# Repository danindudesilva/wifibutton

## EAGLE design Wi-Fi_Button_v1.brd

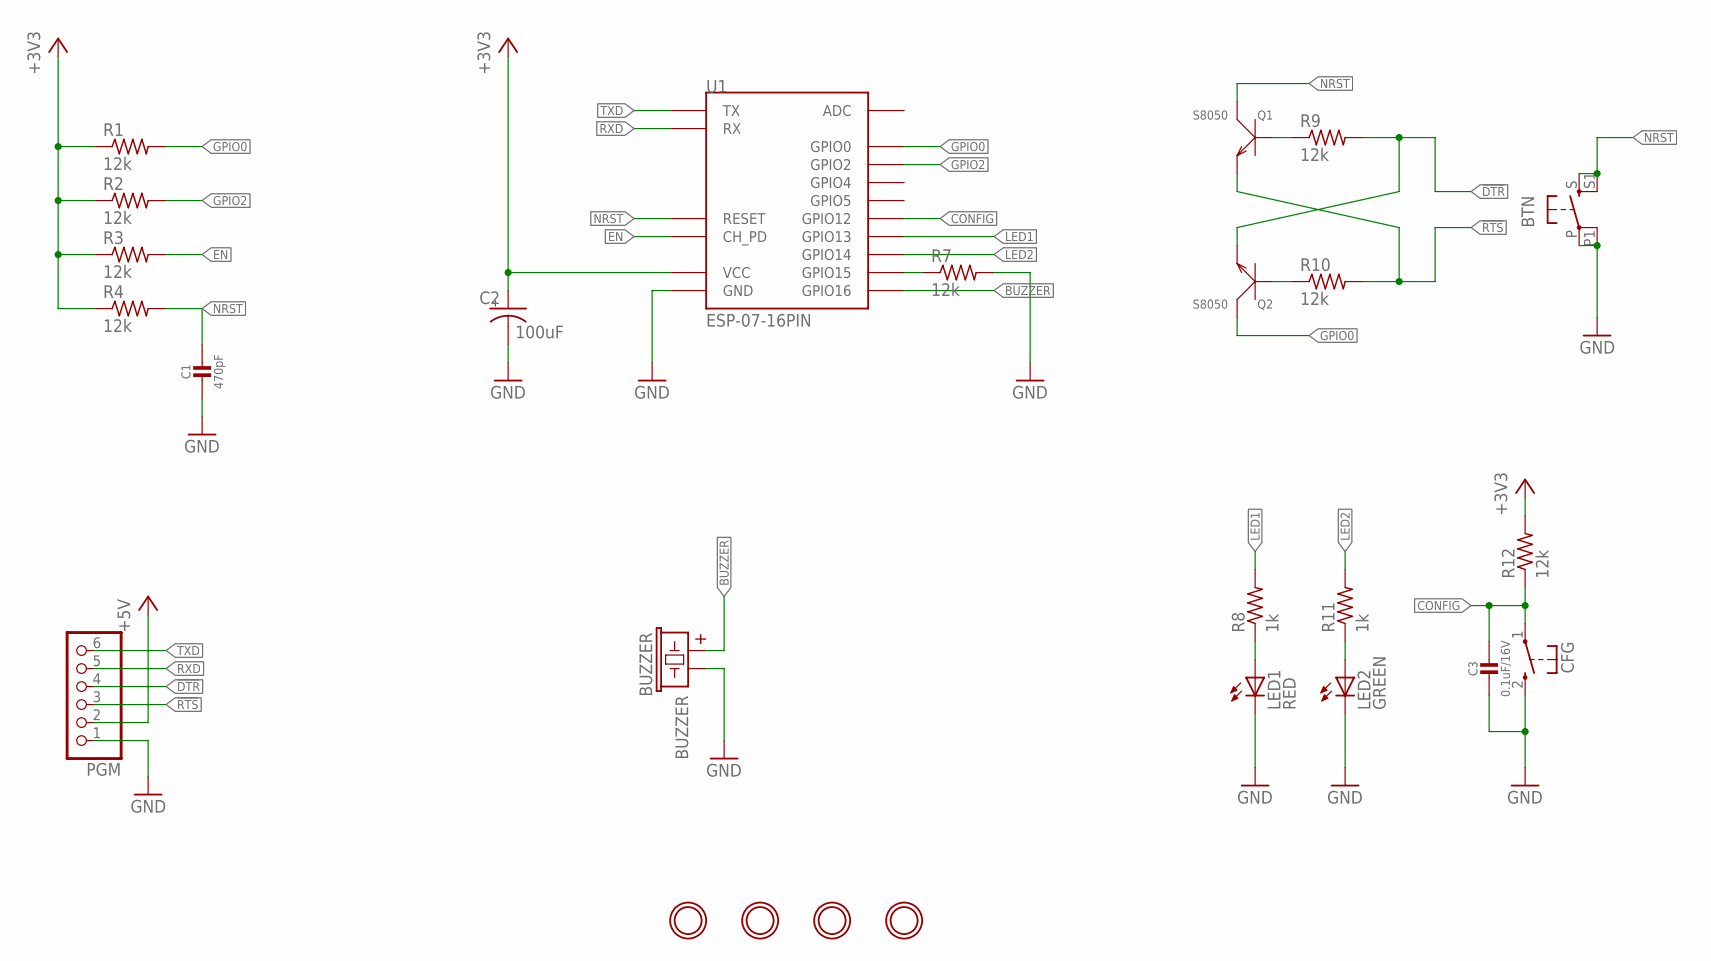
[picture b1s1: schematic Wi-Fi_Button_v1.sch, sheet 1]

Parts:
$H1, $H2, $H3, $H4: MOUNTINGHOLE2.5; MOUNTINGHOLE_2.5_PLATED
BTN: SWITRONIC_12XXS; SWITRONIC_12X12
BUZZER: BUZZER; BUUZER-HN9605B
C1: 470pF; _0805
C2: 100uF; A/3216-18R
C3: 0.1uF/16V; _0805
CFG: KSS-2EG4430
LED1: RED; CHIP-LED0805
LED2: GREEN; CHIP-LED0805
PGM: PINHD-1X6; 1X06
Q1, Q2: S8050; SOT-23
R1, R2, R3, R4, R7, R9, R10, R12: 12k; M0805
R8, R11: 1k; M0805
U1: ESP-07-16PIN

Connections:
!DTR: PGM.4, Q2.2 (E), R9.2
!RTS: PGM.3, Q1.2 (E), R10.2
+3V3: C2.+, R1.1, R2.1, R3.1, R4.1, R12.2, U1.VCC; also elsewhere on the board
+5V: PGM.2; also elsewhere on the board
BUZZER: BUZZER.1, U1.GPIO16
CONFIG: C3.1, CFG.1, R12.1, U1.GPIO12
EN: R3.2, U1.CH_PD
GND: BTN.P, BTN.P1, BUZZER.2, C1.2, C2.-, C3.2, CFG.2 (S), LED1.C, LED2.C, PGM.1, R7.2, U1.GND; also elsewhere on the board
GPIO0: Q2.3 (C), R1.2, U1.GPIO0
GPIO2: R2.2, U1.GPIO2
LED1: R8.2, U1.GPIO13
LED2: R11.2, U1.GPIO14
unnamed: Q1.1 (B), R9.1
unnamed: Q2.1 (B), R10.1
unnamed: R7.1, U1.GPIO15
unnamed: LED1.A, R8.1
unnamed: LED2.A, R11.1
NRST: BTN.S, BTN.S1, C1.1, Q1.3 (C), R4.2, U1.REST (RESET)
RXD: PGM.5, U1.RX
TXD: PGM.6, U1.TX

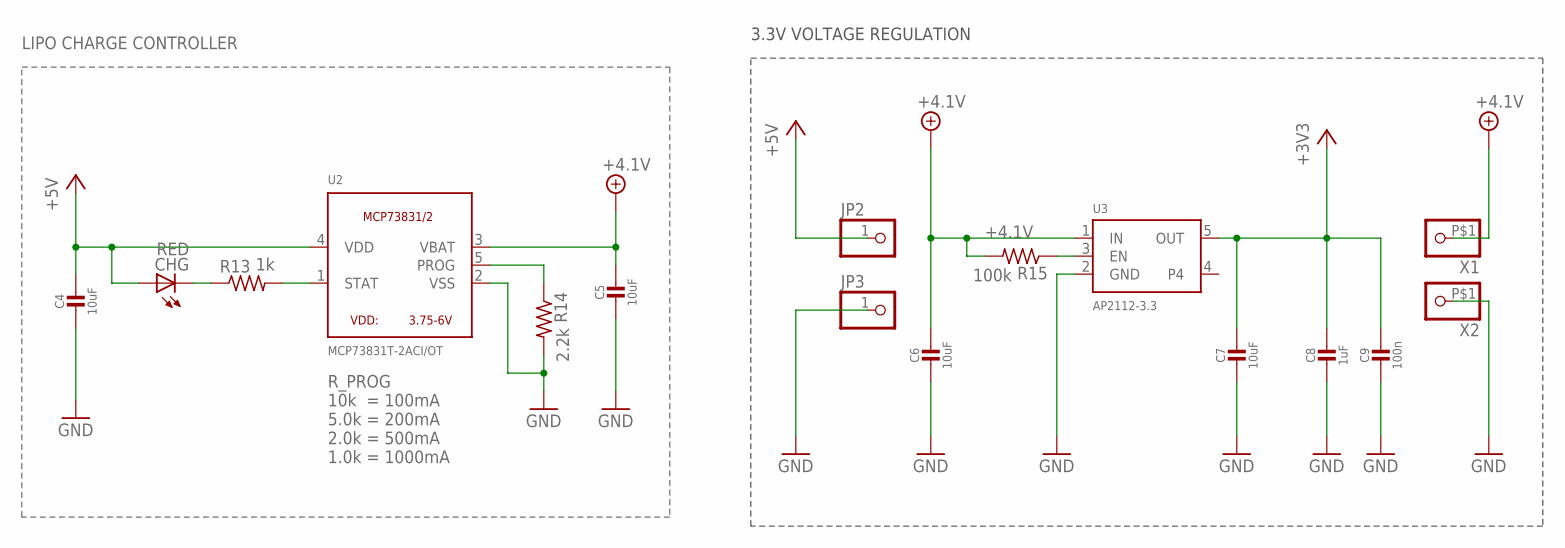
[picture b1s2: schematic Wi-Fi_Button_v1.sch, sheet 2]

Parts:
C4, C5, C6, C7: 10uF; _0805
C8: 1uF; _0805
C9: 100n; _0805
CHG: RED; CHIP-LED0805
JP2, JP3: HEADER-1X1-SMD_MASKHELD_2X2MM; 1X01_SMD_MASKHELD_2X2MM
R13: 1k; M0805
R14: 2.2k; M0805
R15: 100k; M0805
U2: MCP73831T-2ACI/OT; SOT23-5
U3: AP2112-3.3; SOT23-5
X1, X2: A23_PCB_MOUNT

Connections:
+3V3: C7.1, C8.1, C9.1, U3.5 (OUT); also elsewhere on the board
+4.1V: C5.1, C6.1, R15.2, U2.3 (VBAT), U3.1 (IN), X1.P$1
+5V: C4.1, CHG.A, JP2.1, U2.4 (VDD); also elsewhere on the board
GND: C4.2, C5.2, C6.2, C7.2, C8.2, C9.2, JP3.1, R14.2, U2.2 (VSS), U3.2 (GND), X2.P$1; also elsewhere on the board
unnamed: R15.1, U3.3 (EN)
unnamed: CHG.C, R13.1
unnamed: R13.2, U2.1 (STAT)
unnamed: R14.1, U2.5 (PROG)

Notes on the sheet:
3.3V VOLTAGE REGULATION
R_PROG 10k = 100mA 5.0k = 200mA 2.0k = 500mA 1.0k = 1000mA
LIPO CHARGE CONTROLLER

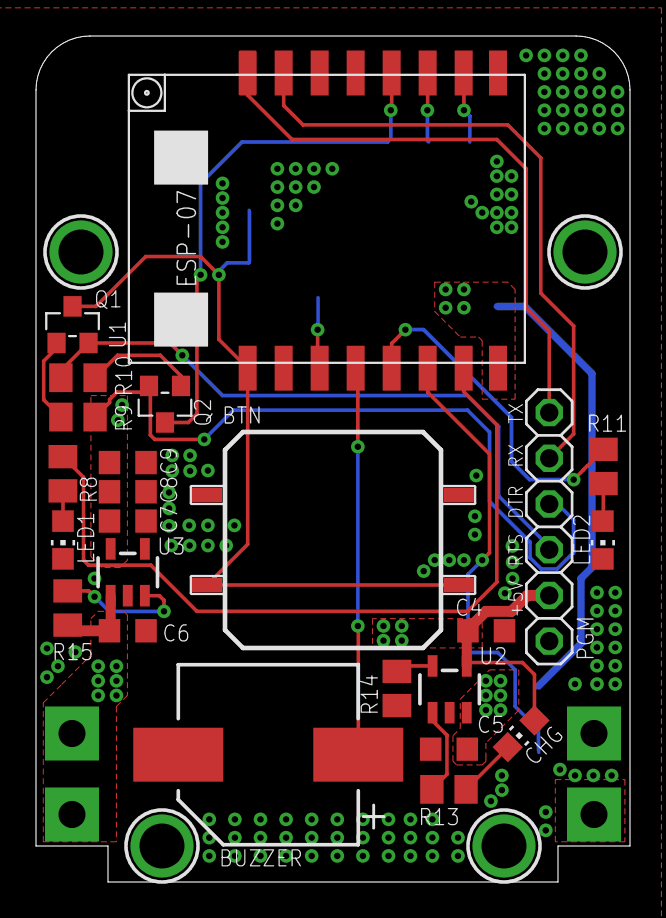
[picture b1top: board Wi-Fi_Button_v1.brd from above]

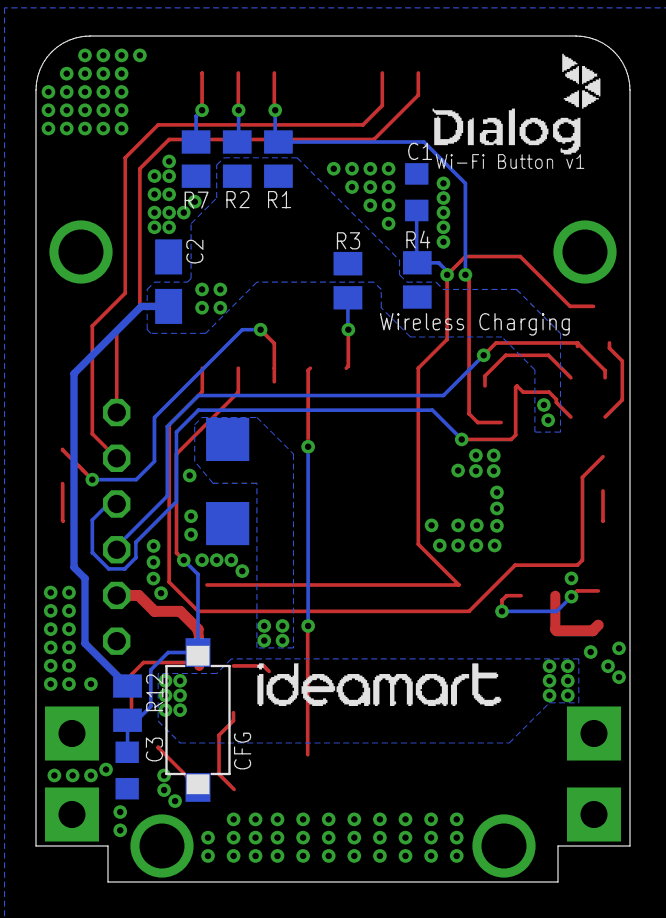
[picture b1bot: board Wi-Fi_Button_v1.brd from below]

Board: 2 copper layers, 33.0 x 47.0 mm, 42 parts (12 on the bottom side), 25 nets.

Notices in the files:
parts and their libraries:
SparkFun-Electromechanical: Licensing: Creative Commons ShareAlike 4.0 International - https://creativecommons.org/licenses/by-sa/4.0
